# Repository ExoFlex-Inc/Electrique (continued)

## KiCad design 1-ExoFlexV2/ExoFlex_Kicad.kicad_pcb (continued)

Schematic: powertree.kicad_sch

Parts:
C3, C5, C12: 100uF 20% 35V; CAP_K1V101P_PAN; PART NUMBER EEE-FK1V101P
C4: 33uF 50V X7R; CAPC6153X500N; PART NUMBER KCM55WR71H336MH01L
C6: 2,2uF 35V X5R; C_0603_1608Metric; PART NUMBER GRM188R6YA225KA12D
C7, C8: 4,7uF 35V X7R; C_0805_2012Metric; PART NUMBER GRM21BZ7YA475KE15K
C9: 0,47uF 6,3V X5R; C_01005_0402Metric; PART NUMBER GRM022R60J474ME15L
C10: 47nF 6,3V X5R; C_01005_0402Metric; PART NUMBER GRM022R60J473ME15L
C11, C213, C214: 1uF 10% 20V; CAPMP3216X180N; PART NUMBER T491A105K020AT
C13, C14: 47uF 10V X5R; C_0805_2012Metric; PART NUMBER GRM21BR61A476ME15L
C15, C16: 330uF 10% 10V; CAPMP7.6X4.3_3.1N_KEM; PART NUMBER T495D337K010ATE150
D6, D9: TVS; DPY2_TEX; PART NUMBER TPD1E05U06DPYR
D116, D117, D118: LED; WL-SMCW_0603; PART NUMBER 150060RS75000
J5, J6: Jumper; PinHeader_1x03_P2.54mm_Vertical; PART NUMBER 61300311121
J7, J71: Jumper 5,2A; PinHeader_1x03_P2.54mm_Vertical; PART NUMBER MTLW-103-07-G-S-230
J8: USB-C; MOLEX_1054500101; PARTREV A7
J81: 14 AWG; PHOENIX_1755736; PART NUMBER 1755736
L1, L2: 1uH 20% 2,3A; L_1210_3225Metric; PART NUMBER BWQC003225161R0MH1
L3: 10uH 10% 150mA; INDC2012X145N; PART NUMBER LBR2012T100K
R5: 5.9k 1% 1/20W; R_0201_0603Metric; PART NUMBER ERJ-1GNF5901C
R6: 100 1% 1/10W; R_0603_1608Metric; PART NUMBER ERJ-3EKF1000V
R7: 8.45k 1% 1/20W; R_0201_0603Metric; PART NUMBER ERJ-1GNF8451C
R46, R47, R185: 270 1% 1/4W; R_0805_2012Metric; PART NUMBER ERJ-PB6B2700V
R55: 530 1% 0,1W; R_0603_1608Metric; PART NUMBER RN73H1JTTD5300F25
R57: 270 1% 1/10W; R_0603_1608Metric; PART NUMBER ERJ-3EKF2700V
R58: 820 1% 1/10W; R_0603_1608Metric; PART NUMBER ERJ-3EKF8200V
R73: 240 1% 1/10W; R_0603_1608Metric; PART NUMBER ERJ-3EKF2400V
R74: 720 1% 1/10W; R_0603_1608Metric; PART NUMBER CRCW0603720RFKTA
R76, R112: 5.1K 1% 1/10W; R_0603_1608Metric; PART NUMBER ERJ-3EKF5101V
TP6, TP7, TP8, TP9, TP10: TestPoint; KEYSTONE_5005; PART NUMBER 5005
U5: DCDC24V/8V; PTN78060WAD; PART NUMBER PTN78060WAD
U6: DCDC24V/5V NUM; NDY0011A_L; PART NUMBER LMZ23610TZ/NOPB
U7: DCDC 24V/-7,8V ANA; PTN78000; PART NUMBER PTN78000AAH
U14: TVS 24V; SOT-23-3_DBZ_TEX; PART NUMBER TSM36ADBZR
U123: LDO -5VA; TO92260P482H934-3N; PART NUMBER LM337LZ/LFT3
U124: LDO 5VA; T03B_TEX; PART NUMBER LM338T/NOPB

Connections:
+5V: J7.1, J8.A4 (VBUS_A4), J8.A9 (VBUS_A9), J8.B4 (VBUS_B4), J8.B9 (VBUS_B9), J71.1, J81.1; also elsewhere on the board
+5VA: J5.1; also elsewhere on the board
+24V: L1.1, L2.1, L3.1; also elsewhere on the board
-5VA: J6.1; also elsewhere on the board
GND: C3.2, C4.2, C5.2, C6.2, C7.2, C8.2, C9.2, C10.2, C11.2, C12.1, C13.2, C14.2, C15.2, C16.2, C213.2, C214.2, D6.2 (A), D9.2 (A), D116.1 (K), D117.1 (K), D118.2 (A), J8.A1 (GND_A1), J8.A12 (GND_A12), J8.B1 (GND_B1), J8.B12 (GND_B12), J8.SH1 (SHIELD3), J8.SH2 (SHIELD4), J8.SH3 (SHIELD1), J8.SH4 (SHIELD2), J81.2, R5.1, R6.1, R58.1, R74.1, R76.1, R112.2, U5.1 (GND), U5.7 (GND), U6.3 (SYNC), U6.5 (AGND), U6.6 (AGND), U6.12 (EP), U7.P5 (GND), U14.1 (GND), U14.2 (GND); also elsewhere on the board
unnamed: C4.1, L1.2, U6.1 (VIN), U6.2 (VIN)
unnamed: C5.1, C7.1, C8.1, L3.2, U7.P2 (VIN)
unnamed: C6.1, L2.2, U5.2 (VI)
unnamed: C9.1, U6.8 (SS)
unnamed: C10.1, C13.1, C14.1, C15.1, C16.1, J7.2, J71.2, R55.2, R185.2, TP9.TP, U6.10 (VOUT), U6.11 (VOUT), U14.3 (IO)
unnamed: C11.1, C12.2, R7.1, TP6.TP, U7.P1 (VOUT), U123.3 (IN)
unnamed: C3.1, C213.1, TP10.TP, U5.5 (SENSE), U5.6 (VO), U124.3 (IN)
unnamed: C214.1, D9.1 (K), J6.2, R47.2, R73.2, TP8.TP, U123.2 (OUT)
unnamed: D6.1 (K), J5.2, R46.2, R57.2, TP7.TP, U124.2 (OUT)
unnamed: D116.2 (A), R185.1
unnamed: D117.2 (A), R46.1
unnamed: D118.1 (K), R47.1
unnamed: J7.3, J71.3
unnamed: J8.A5 (CC1), R76.2
unnamed: J8.B5 (CC2), R112.1
unnamed: R5.2, U5.4 (VOADJUST)
unnamed: R7.2, U7.P4 (SET)
unnamed: R6.2, R55.1, U6.7 (FB)
unnamed: R57.1, R58.2, U124.1 (ADJ)
unnamed: R73.1, R74.2, U123.1 (ADJ)

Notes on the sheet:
REV 1
__HS HERE__
15/07/2024 - Louis-Daniel Gaulin
Vers PI5 5V
Régulateur 5VNUM: 24V @ 1,45A Régulateur 5VA : 24 @ 110mA Régulateur -5VA : 24 @ 25mA Contacteur : 24V @ 110mA Total Current : 24V @ 1,695A

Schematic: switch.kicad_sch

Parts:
D39, D40, D41, D42, D47, D48, D49, D50, D55, D56: TVS; DPY2_TEX; PART NUMBER TPD1E05U06DPYR
J25, J26, J27, J28, J29, J30, J31, J32, J33, J34: 2POS; CON_39281023; PART NUMBER 0039281023
R11, R12, R13, R14, R15, R16, R17, R18, R19, R20: 1K 1% 1/10W; R_0603_1608Metric; PART NUMBER ERJ-3EKF1001V

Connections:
+5V: R11.2, R12.2, R13.2, R14.2, R15.2, R16.2, R17.2, R18.2, R19.2, R20.2; also elsewhere on the board
GND: D39.2 (A), D40.2 (A), D41.2 (A), D42.2 (A), D47.2 (A), D48.2 (A), D49.2 (A), D50.2 (A), D55.2 (A), D56.2 (A); also elsewhere on the board
MAX_SW_1: D39.1 (K), J25.2; also elsewhere on the board
MAX_SW_2: D41.1 (K), J27.2; also elsewhere on the board
MAX_SW_3: D47.1 (K), J29.2; also elsewhere on the board
MAX_SW_4: D49.1 (K), J31.2; also elsewhere on the board
MAX_SW_5: D50.1 (K), J32.2; also elsewhere on the board
MIN_SW_1: D40.1 (K), J26.2; also elsewhere on the board
MIN_SW_2: D42.1 (K), J28.2; also elsewhere on the board
MIN_SW_3: D48.1 (K), J30.2; also elsewhere on the board
unnamed: J25.1, R14.1
unnamed: J26.1, R11.1
unnamed: J27.1, R12.1
unnamed: J28.1, R13.1
unnamed: J29.1, R15.1
unnamed: J30.1, R16.1
unnamed: J31.1, R17.1
unnamed: J32.1, R18.1
unnamed: J33.1, R19.1
unnamed: J34.1, R20.1
RESET: D56.1 (K), J34.2; also elsewhere on the board
URG_USER: D55.1 (K), J33.2; also elsewhere on the board

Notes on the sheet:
RESET
SWMIN2
URG1
SWMAX3
SWMIN1
SWMAX1
SWMIN3
10xRes1k : 5V @ 50mA Total current : 5V @ 52,5mA
SWMAX5
SWMAX4
SWMAX2

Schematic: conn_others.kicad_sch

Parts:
D100, D101, D102, D103, D104, D106, D108: TVS; DPY2_TEX; PART NUMBER TPD1E05U06DPYR
J52: 2POS; CON_39281023; PART NUMBER 0039281023
J53, J54: 3POS; CON_39301039; PARTREV 03.03.2021
J57: 6POS; PinSocket_1x06_P2.54mm_Vertical; PART NUMBER SMC-1-06-1-GT

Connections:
+5V: D104.1 (K), J57.1; also elsewhere on the board
+5VA: J53.3, J54.3; also elsewhere on the board
/CONNECTOR (OTHERS)/CANH: D101.1 (K), J52.1, J57.5
/CONNECTOR (OTHERS)/CANL: D103.1 (K), J52.2, J57.6
CAN_RD: D100.1 (K), J57.4; also elsewhere on the board
CAN_TD: D102.1 (K), J57.3; also elsewhere on the board
GND: D100.2 (A), D101.2 (A), D102.2 (A), D103.2 (A), D104.2 (A), D106.2 (A), D108.2 (A), J53.1, J54.1, J57.2; also elsewhere on the board
TEMP_OUT_1: D106.1 (K), J53.2; also elsewhere on the board
TEMP_OUT_2: D108.1 (K), J54.2; also elsewhere on the board

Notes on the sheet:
Notes :
Bus Adapter : 5V @ 75mA 2xTempSensor : N/A (uA) Total current : 5V @ 78,75mA
Temp 2
CAN Bus
Temp 1

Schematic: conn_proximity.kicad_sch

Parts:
D59, D60, D61, D62, D67, D68, D69, D70, D71, D72, D73, D74: TVS; DPY2_TEX; PART NUMBER TPD1E05U06DPYR
J35, J36, J37, J38: 2POS; CON_39281023; PART NUMBER 0039281023
J39, J40, J41, J42: 4POS; CON_39301049; PARTREV 03.03.2021
R21, R22, R23, R24: 1K 1% 1/10W; R_0603_1608Metric; PART NUMBER ERJ-3EKF1001V
R25, R26, R27, R28: 100K 1% 1/10W; R_0603_1608Metric; PART NUMBER ERJ-3EKF1003V
R114, R120: 165 1% 1/20W; R_0201_0603Metric; PART NUMBER ERJ-1GNF1650C
R119, R168: 464 1% 1/20W; R_0201_0603Metric; PART NUMBER ERJ-1GNF4640C

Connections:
+5V: R21.2, R22.2, R23.2, R24.2, R25.1, R26.1, R27.1, R28.1, R114.1, R119.1, R120.1, R168.1; also elsewhere on the board
BUT_PROX_LEFT1: D59.1 (K), J35.2; also elsewhere on the board
BUT_PROX_LEFT2: D60.1 (K), J36.2; also elsewhere on the board
BUT_PROX_RIGHT1: D61.1 (K), J37.2; also elsewhere on the board
BUT_PROX_RIGHT2: D62.1 (K), J38.2; also elsewhere on the board
EMI_PROX1: D71.1 (K), J39.2
EMI_PROX1_INT: D67.1 (K), J39.4, R25.2; also elsewhere on the board
EMI_PROX2: D73.1 (K), J41.2
EMI_PROX2_INT: D69.1 (K), J41.4, R27.2; also elsewhere on the board
GND: D59.2 (A), D60.2 (A), D61.2 (A), D62.2 (A), D67.2 (A), D68.2 (A), D69.2 (A), D70.2 (A), D71.2 (A), D72.2 (A), D73.2 (A), D74.2 (A), J39.1, J40.1, J41.1, J42.1; also elsewhere on the board
unnamed: J35.1, R21.1
unnamed: J36.1, R22.1
unnamed: J37.1, R23.1
unnamed: J38.1, R24.1
unnamed: J39.3, R114.2
unnamed: J40.3, R119.2
unnamed: J41.3, R120.2
unnamed: J42.3, R168.2
REC_PROX1: D72.1 (K), J40.2; also elsewhere on the board
REC_PROX1_INT: D68.1 (K), J40.4, R26.2; also elsewhere on the board
REC_PROX2: D74.1 (K), J42.2; also elsewhere on the board
REC_PROX2_INT: D70.1 (K), J42.4, R28.2; also elsewhere on the board

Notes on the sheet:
Emi Prox 2
But Prox L2
Rec Prox 1
Emi Prox 1
But Prox R1
Rec Prox 2
But Prox R2
But Prox L1
4xRes1k : 5V @ 20mA 4xRes100k : 5V @ 0,2mA 2x165 : 5V @ 30mA 2x464 : 5V @ 10,7mA Total current : 5V @ 64mA

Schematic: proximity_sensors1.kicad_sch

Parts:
C38, C39, C40, C41: 10uF 10V X7R; C_0805_2012Metric; PART NUMBER GRM21BR71A106KA73L
C42, C43: 10nF 50V; C_0805_2012Metric; PART NUMBER GRM2195C1H103JA01D
J95, J96, J97, J98, J99, J100: Jumper; PinHeader_1x03_P2.54mm_Vertical; PART NUMBER 61300311121
R121, R122, R123, R124: 10K 1% 1/10W; R_0603_1608Metric; PART NUMBER ERJ-3EKF1002V
R125, R126, R127, R128: 5.1K 1% 1/10W; R_0603_1608Metric; PART NUMBER ERJ-3EKF5101V
R129, R130: 0Ω; R_0805_2012Metric; PART NUMBER ERJ-6GEY0R00V
R131, R132, R133, R134, R135, R136: 100K 1% 1/10W; R_0603_1608Metric; PART NUMBER ERJ-3EKF1003V
TP92, TP93: TestPoint; KEYSTONE_5005; PART NUMBER 5005
U45, U46, U47: Inverter; SN74LVC3G14DCUT; PART NUMBER SN74LVC3G14DCUT
U62, U63, U64, U65: AND Gate; SOT95P270X145-5N; PART NUMBER SN74LVC1G08DBVR

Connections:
+5V: R131.2, R132.2, R133.2, R134.2, R135.2, R136.2, U45.8 (VCC), U46.8 (VCC), U47.8 (VCC), U62.5 (VCC), U63.5 (VCC), U64.5 (VCC), U65.5 (VCC); also elsewhere on the board
BUT_PROX_LEFT1: R121.1, R125.1; also elsewhere on the board
BUT_PROX_LEFT2: R122.1, R126.1; also elsewhere on the board
BUT_PROX_RIGHT1: R123.1, R127.1; also elsewhere on the board
BUT_PROX_RIGHT2: R124.1, R128.1; also elsewhere on the board
GND: C38.2, C39.2, C40.2, C41.2, C42.2, C43.2, R121.2, R122.2, R123.2, R124.2, U45.4 (GND), U46.4 (GND), U46.5 (2Y), U46.6 (3A), U47.3 (2A), U47.4 (GND), U47.6 (3A), U62.3 (GND), U63.3 (GND), U64.3 (GND), U65.3 (GND); also elsewhere on the board
M_BUT_PROX_L1: J98.2, U64.1 (A); also elsewhere on the board
M_BUT_PROX_L2: J97.2, U64.2 (B); also elsewhere on the board
M_BUT_PROX_R1: J95.2, U62.1 (A); also elsewhere on the board
M_BUT_PROX_R2: J99.2, U62.2 (B); also elsewhere on the board
M_REC_PROX1: J100.2, U63.1 (A); also elsewhere on the board
M_REC_PROX2: J96.2, U63.2 (B); also elsewhere on the board
unnamed: C38.1, R125.2, U45.1 (1A)
unnamed: C39.1, R126.2, U45.3 (2A)
unnamed: C40.1, R127.2, U45.6 (3A)
unnamed: C41.1, R128.2, U46.1 (1A)
unnamed: C42.1, J100.1, R129.2
unnamed: C43.1, J96.1, R130.2
unnamed: J95.1, U45.2 (3Y)
unnamed: J95.3, R131.1
unnamed: J96.3, R132.1
unnamed: J97.1, U45.5 (2Y)
unnamed: J97.3, R133.1
unnamed: J98.1, U45.7 (1Y)
unnamed: J98.3, R134.1
unnamed: J99.1, U46.7 (1Y)
unnamed: J99.3, R135.1
unnamed: J100.3, R136.1
unnamed: U47.1 (1A), U65.4 (Y)
unnamed: U62.4 (Y), U65.2 (B)
unnamed: U64.4 (Y), U65.1 (A)
PROX_BUT_SEC: TP92.TP, U47.7 (1Y); also elsewhere on the board
PROX_OPTO_SEC: TP93.TP, U63.4 (Y); also elsewhere on the board
REC_PROX1: R129.1; also elsewhere on the board
REC_PROX2: R130.1; also elsewhere on the board

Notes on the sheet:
Do not populate
4xANDGate : 5V @ 4mA 5xNOTGate : 5V @ 5mA Total current : 5V @ 9,55mA
Debouncing

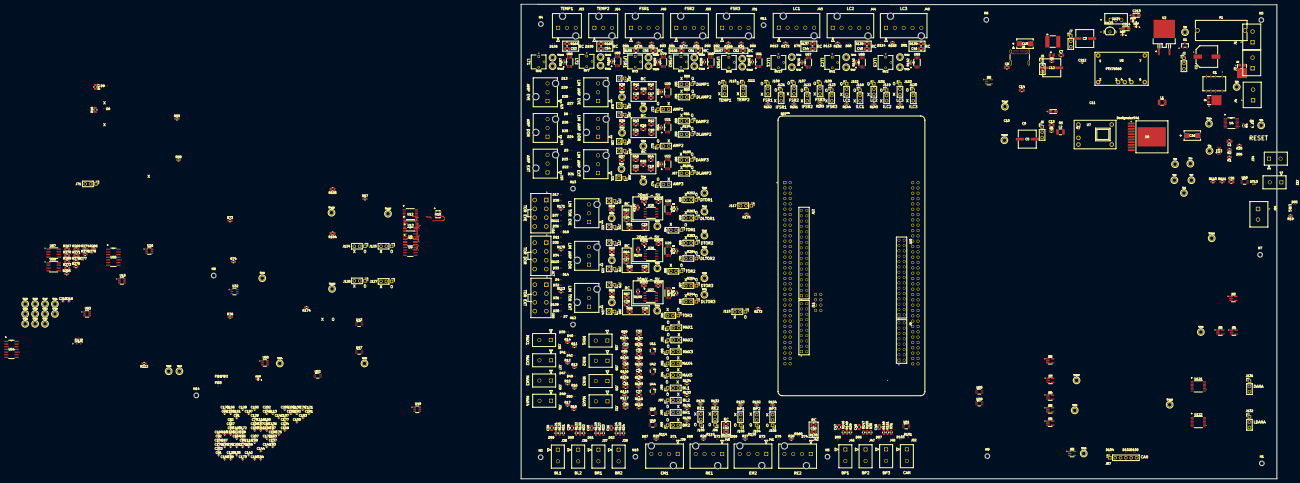
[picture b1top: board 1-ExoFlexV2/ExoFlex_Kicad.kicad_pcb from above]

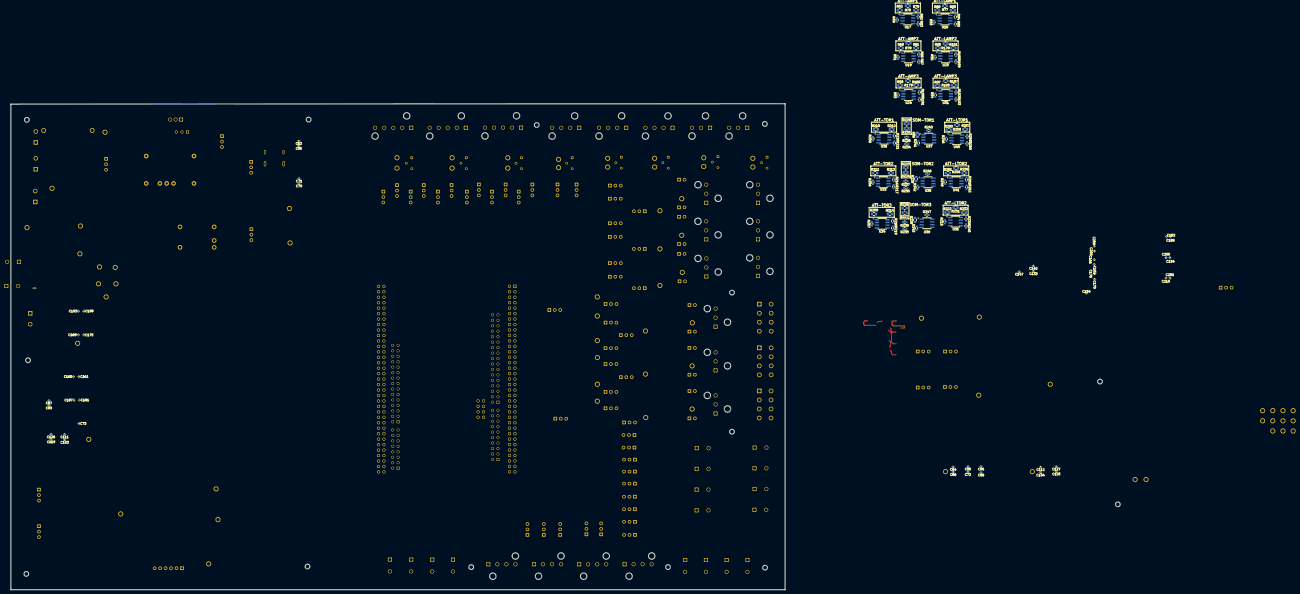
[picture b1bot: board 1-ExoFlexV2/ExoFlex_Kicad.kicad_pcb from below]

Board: 4 copper layers, 360.3 x 226.2 mm, 849 parts (150 on the bottom side), 438 nets.

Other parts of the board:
J55, J56, J58, J59, J66, J67: Jumper; PinHeader_1x03_P2.54mm_Vertical
R49, R50, R51, R82, R83, R84, R85, R86, R87, R92, R93, R94, R188, R189, R190, R191, R192, R193: 10K 1% 1/10W; R_0603_1608Metric
R52, R68, R69, R70, R77, R78, R95, R96, R97, R178, R179, R180: 3.3k 1% 1/8W; R_0805_2012Metric
R79, R80, R81, R181, R186, R187: 0Ω; R_0805_2012Metric
R88, R90, R91, R194, R195, R196: 100k 1% 1/20W; R_0201_0603Metric
U17, U18, U19, U23, U24, U31: OP_AMP2; SOIC127P599X175-8N

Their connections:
+5VA: U17.8 (VCC+), U18.8 (VCC+), U19.8 (VCC+), U23.8 (VCC+), U24.8 (VCC+), U31.8 (VCC+); also elsewhere on the board
-5VA: U17.4 (VCC-), U18.4 (VCC-), U19.4 (VCC-), U23.4 (VCC-), U24.4 (VCC-), U31.4 (VCC-); also elsewhere on the board
DOR_AMP_DATA: J58.2; also elsewhere on the board
DOR_AMP_DATA1: R51.1; also elsewhere on the board
DOR_AMP_LIM_DATA: J59.2; also elsewhere on the board
DOR_AMP_LIM_DATA1: R92.1; also elsewhere on the board
EVE_AMP_DATA: J55.2; also elsewhere on the board
EVE_AMP_DATA1: R49.1; also elsewhere on the board
EVE_AMP_LIM_DATA: J56.2; also elsewhere on the board
EVE_AMP_LIM_DATA1: R50.1; also elsewhere on the board
EXT_AMP_DATA: J66.2; also elsewhere on the board
EXT_AMP_DATA1: R93.1; also elsewhere on the board
EXT_AMP_LIM_DATA: J67.2; also elsewhere on the board
EXT_AMP_LIM_DATA1: R94.1; also elsewhere on the board
GND: R88.2, R90.2, R91.2, R194.2, R195.2, R196.2, U17.3 (1IN+), U17.5 (2IN+), U18.3 (1IN+), U18.5 (2IN+), U19.3 (1IN+), U19.5 (2IN+), U23.3 (1IN+), U23.5 (2IN+), U24.3 (1IN+), U24.5 (2IN+), U31.3 (1IN+), U31.5 (2IN+); also elsewhere on the board
unnamed: J55.1, R83.1, U17.7 (2OUT)
unnamed: J55.3, R88.1
unnamed: J56.1, R85.1, U18.7 (2OUT)
unnamed: J56.3, R90.1
unnamed: J58.1, R87.1, U19.7 (2OUT)
unnamed: J58.3, R91.1
unnamed: J59.1, R189.1, U23.7 (2OUT)
unnamed: J59.3, R194.1
unnamed: J66.1, R191.1, U24.7 (2OUT)
unnamed: J66.3, R195.1
unnamed: J67.1, R193.1, U31.7 (2OUT)
unnamed: J67.3, R196.1
unnamed: R49.2, R52.1, U17.2 (1IN-)
unnamed: R50.2, R68.1, U18.2 (1IN-)
unnamed: R51.2, R69.1, U19.2 (1IN-)
unnamed: R52.2, R70.1
unnamed: R68.2, R77.1
unnamed: R69.2, R78.1
unnamed: R70.2, R79.1
unnamed: R77.2, R80.1
unnamed: R78.2, R81.1
unnamed: R79.2, R82.2, U17.1 (1OUT)
unnamed: R80.2, R84.2, U18.1 (1OUT)
unnamed: R81.2, R86.2, U19.1 (1OUT)
unnamed: R82.1, R83.2, U17.6 (2IN-)
unnamed: R84.1, R85.2, U18.6 (2IN-)
unnamed: R86.1, R87.2, U19.6 (2IN-)
unnamed: R92.2, R95.1, U23.2 (1IN-)
unnamed: R93.2, R96.1, U24.2 (1IN-)
unnamed: R94.2, R97.1, U31.2 (1IN-)
unnamed: R95.2, R178.1
unnamed: R178.2, R181.1
unnamed: R96.2, R179.1
unnamed: R179.2, R186.1
unnamed: R97.2, R180.1
unnamed: R180.2, R187.1
unnamed: R181.2, R188.2, U23.1 (1OUT)
unnamed: R186.2, R190.2, U24.1 (1OUT)
unnamed: R187.2, R192.2, U31.1 (1OUT)
unnamed: R188.1, R189.2, U23.6 (2IN-)
unnamed: R190.1, R191.2, U24.6 (2IN-)
unnamed: R192.1, R193.2, U31.6 (2IN-)

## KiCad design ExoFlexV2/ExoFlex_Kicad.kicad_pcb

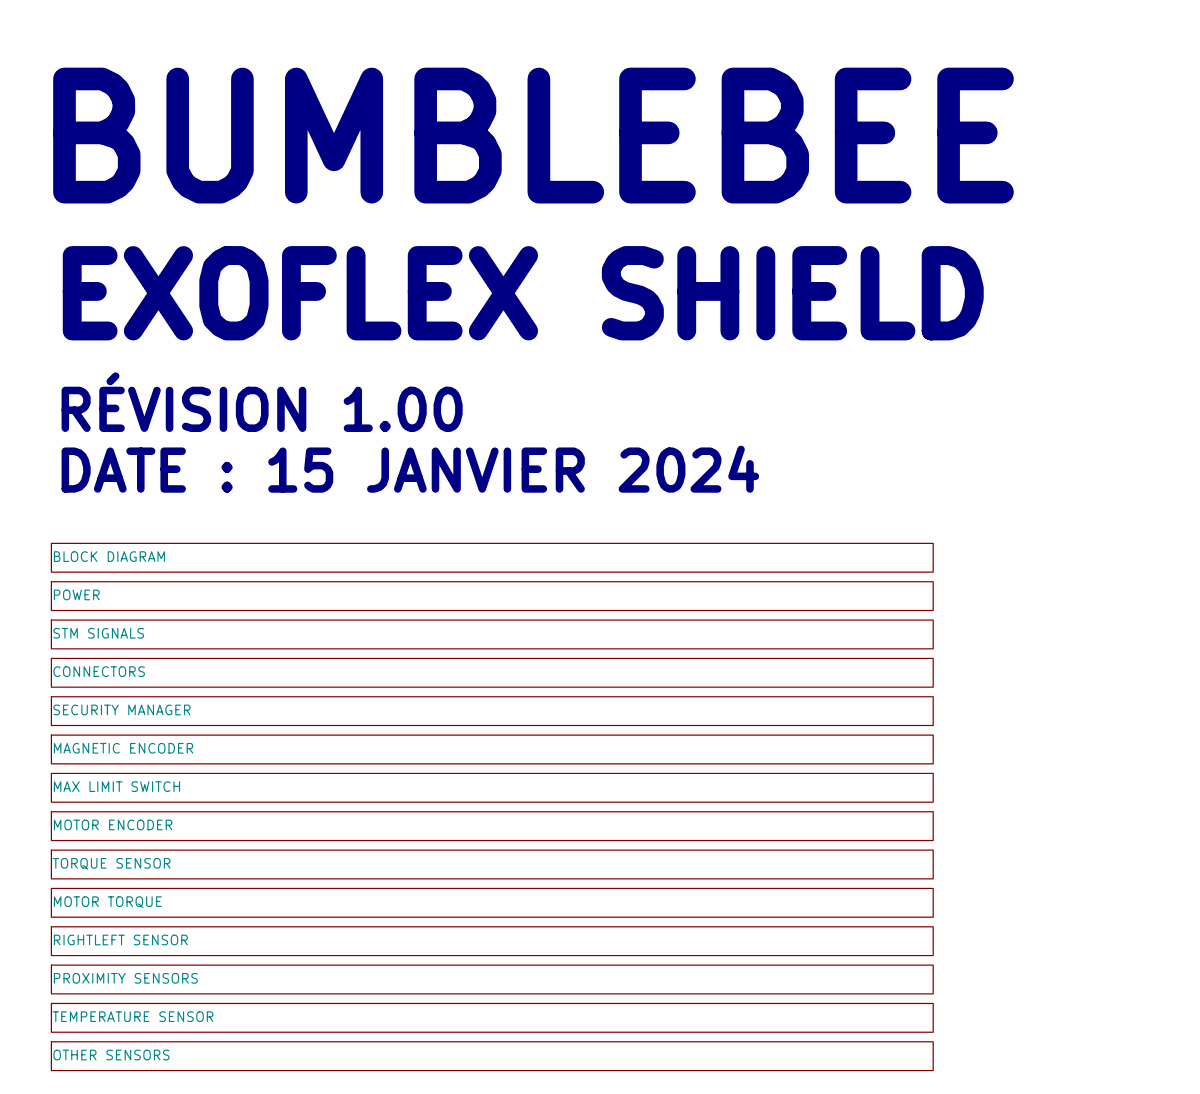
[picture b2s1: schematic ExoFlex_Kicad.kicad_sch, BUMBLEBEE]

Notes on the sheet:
BUMBLEBEE
EXOFLEX SHIELD
RÉVISION 1.00 DATE : 15 JANVIER 2024

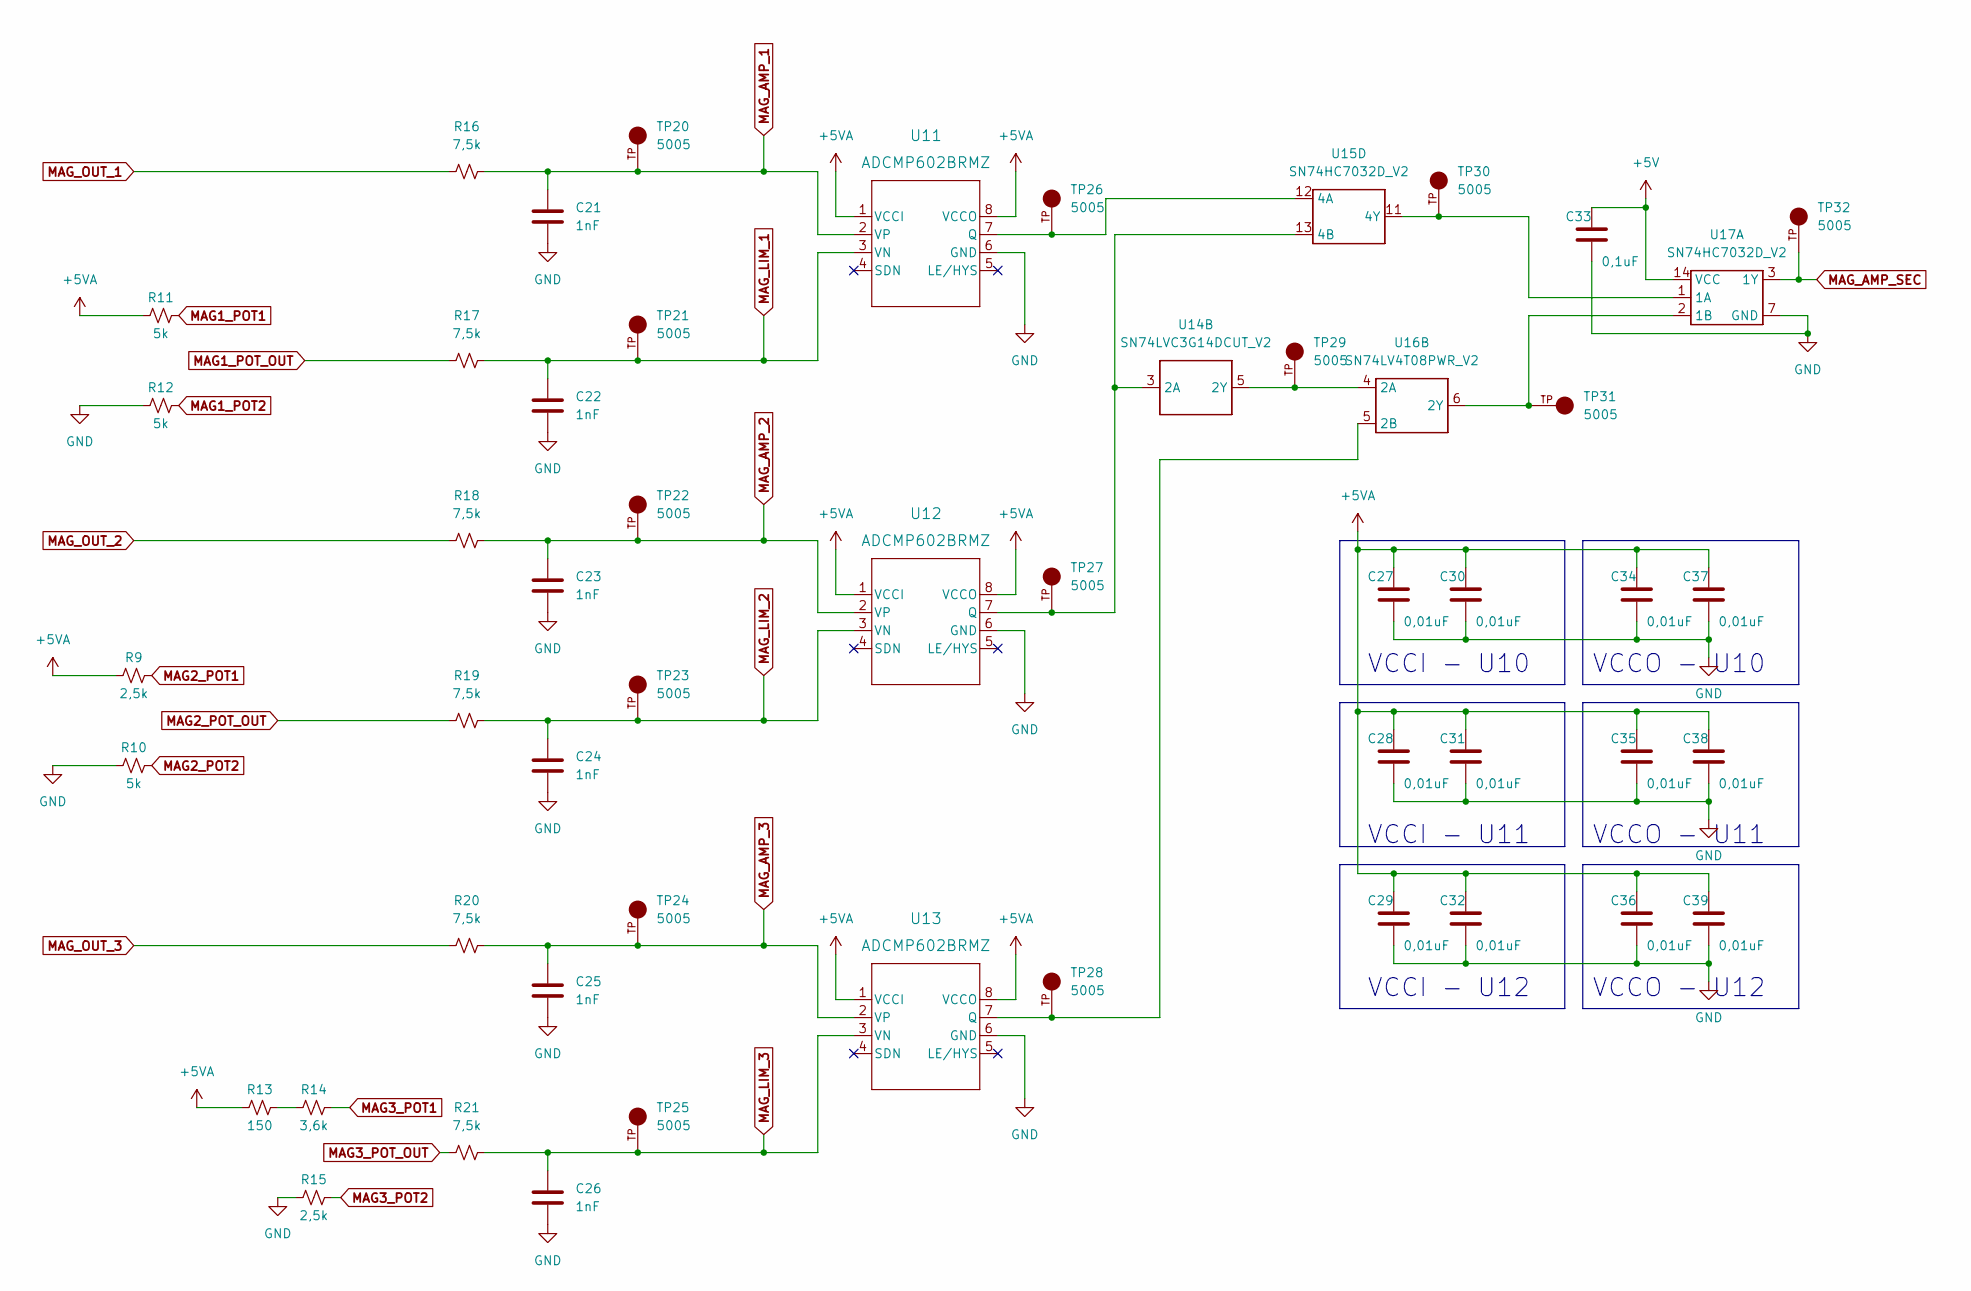
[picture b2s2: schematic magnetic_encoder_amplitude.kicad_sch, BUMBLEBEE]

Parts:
C21, C22, C23, C24, C25, C26: 1nF; C_0603_1608Metric
C27, C28, C29, C30, C31, C32, C34, C35, C36, C37, C38, C39: 0,01uF; C_0603_1608Metric
C33: 0,1uF; C_0603_1608Metric
R9, R15: 2,5k; R_0603_1608Metric
R10, R11, R12: 5k; R_0603_1608Metric
R13: 150; R_0603_1608Metric
R14: 3,6k; R_0603_1608Metric
R16, R17, R18, R19, R20, R21: 7,5k; R_0603_1608Metric
TP20, TP21, TP22, TP23, TP24, TP25, TP26, TP27, TP28, TP29, TP30, TP31, TP32: 5005; KEYSTONE_5005
U11, U12, U13: ADCMP602BRMZ
U14: SN74LVC3G14DCUT_V2; SN74LVC3G14DCUT
U15, U17: SN74HC7032D_V2; SN74HC7032D
U16: SN74LV4T08PWR_V2; SN74LV4T08PWR

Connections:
+5VA: C27.1, C28.1, C29.1, C30.1, C31.1, C32.1, C34.1, C35.1, C36.1, C37.1, C38.1, C39.1, R9.1, R11.1, R13.1, U11.1 (VCCI), U11.8 (VCCO), U12.1 (VCCI), U12.8 (VCCO), U13.1 (VCCI), U13.8 (VCCO); also elsewhere on the board
MAG1_POT1: R11.2; also elsewhere on the board
MAG1_POT2: R12.2; also elsewhere on the board
MAG1_POT_OUT: R17.1; also elsewhere on the board
MAG2_POT1: R9.2; also elsewhere on the board
MAG2_POT2: R10.2; also elsewhere on the board
MAG2_POT_OUT: R19.1; also elsewhere on the board
MAG3_POT1: R14.2; also elsewhere on the board
MAG3_POT2: R15.2; also elsewhere on the board
MAG3_POT_OUT: R21.1; also elsewhere on the board
MAG_AMP_1: C21.1, R16.2, TP20.TP, U11.2 (VP); also elsewhere on the board
MAG_AMP_2: C23.1, R18.2, TP22.TP, U12.2 (VP); also elsewhere on the board
MAG_AMP_3: C25.1, R20.2, TP24.TP, U13.2 (VP); also elsewhere on the board
MAG_AMP_SEC: TP32.TP, U17.3 (1Y); also elsewhere on the board
MAG_LIM_1: C22.1, R17.2, TP21.TP, U11.3 (VN); also elsewhere on the board
MAG_LIM_2: C24.1, R19.2, TP23.TP, U12.3 (VN); also elsewhere on the board
MAG_LIM_3: C26.1, R21.2, TP25.TP, U13.3 (VN); also elsewhere on the board
MAG_OUT_1: R16.1; also elsewhere on the board
MAG_OUT_2: R18.1; also elsewhere on the board
MAG_OUT_3: R20.1; also elsewhere on the board
unnamed: R13.2, R14.1
unnamed: TP26.TP, U11.7 (Q), U15.12 (4A)
unnamed: TP27.TP, U12.7 (Q), U14.3 (2A), U15.13 (4B)
unnamed: TP28.TP, U13.7 (Q), U16.5 (2B)
unnamed: TP29.TP, U14.5 (2Y), U16.4 (2A)
unnamed: TP30.TP, U15.11 (4Y), U17.1 (1A)
unnamed: TP31.TP, U16.6 (2Y), U17.2 (1B)

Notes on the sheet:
VCCO - U11
VCCO - U10
VCCI - U10
VCCO - U12
VCCI - U11
VCCI - U12

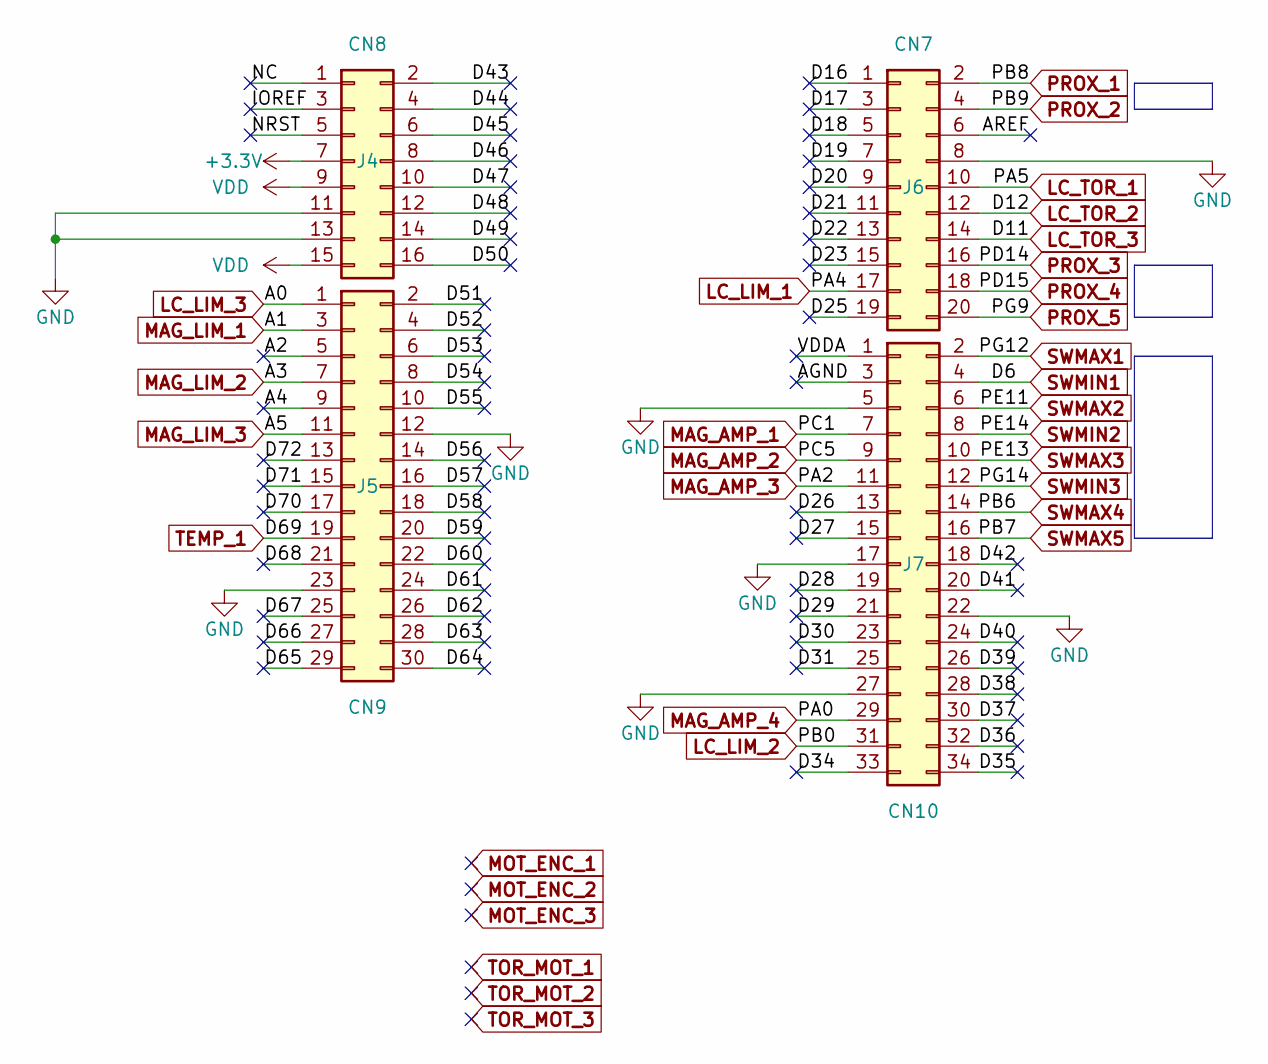
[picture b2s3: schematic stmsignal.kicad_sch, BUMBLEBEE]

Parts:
J4: CN8; PinSocket_2x08_P2.54mm_Vertical
J5: CN9; PinSocket_2x15_P2.54mm_Vertical
J6: CN7; PinSocket_2x10_P2.54mm_Vertical
J7: CN10; PinSocket_2x17_P2.54mm_Vertical

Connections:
+3V3: J4.7
/STM SIGNALS/A2: J5.5
/STM SIGNALS/A4: J5.9
/STM SIGNALS/AGND: J7.3
/STM SIGNALS/AREF: J6.6
/STM SIGNALS/D16: J6.1
/STM SIGNALS/D17: J6.3
/STM SIGNALS/D18: J6.5
/STM SIGNALS/D19: J6.7
/STM SIGNALS/D20: J6.9
/STM SIGNALS/D21: J6.11
/STM SIGNALS/D22: J6.13
/STM SIGNALS/D23: J6.15
/STM SIGNALS/D25: J6.19
/STM SIGNALS/D26: J7.13
/STM SIGNALS/D27: J7.15
/STM SIGNALS/D28: J7.19
/STM SIGNALS/D29: J7.21
/STM SIGNALS/D30: J7.23
/STM SIGNALS/D31: J7.25
/STM SIGNALS/D34: J7.33
/STM SIGNALS/D35: J7.34
/STM SIGNALS/D36: J7.32
/STM SIGNALS/D37: J7.30
/STM SIGNALS/D38: J7.28
/STM SIGNALS/D39: J7.26
/STM SIGNALS/D40: J7.24
/STM SIGNALS/D41: J7.20
/STM SIGNALS/D42: J7.18
/STM SIGNALS/D43: J4.2
/STM SIGNALS/D44: J4.4
/STM SIGNALS/D45: J4.6
/STM SIGNALS/D46: J4.8
/STM SIGNALS/D47: J4.10
/STM SIGNALS/D48: J4.12
/STM SIGNALS/D49: J4.14
/STM SIGNALS/D50: J4.16
/STM SIGNALS/D51: J5.2
/STM SIGNALS/D52: J5.4
/STM SIGNALS/D53: J5.6
/STM SIGNALS/D54: J5.8
/STM SIGNALS/D55: J5.10
/STM SIGNALS/D56: J5.14
/STM SIGNALS/D57: J5.16
/STM SIGNALS/D58: J5.18
/STM SIGNALS/D59: J5.20
/STM SIGNALS/D60: J5.22
/STM SIGNALS/D61: J5.24
/STM SIGNALS/D62: J5.26
/STM SIGNALS/D63: J5.28
/STM SIGNALS/D64: J5.30
/STM SIGNALS/D65: J5.29
/STM SIGNALS/D66: J5.27
/STM SIGNALS/D67: J5.25
/STM SIGNALS/D68: J5.21
/STM SIGNALS/D70: J5.17
/STM SIGNALS/D71: J5.15
/STM SIGNALS/D72: J5.13
/STM SIGNALS/IOREF: J4.3
/STM SIGNALS/NC: J4.1
/STM SIGNALS/NRST: J4.5
/STM SIGNALS/VDDA: J7.1
LC_LIM_1: J6.17; also elsewhere on the board
LC_LIM_2: J7.31; also elsewhere on the board
LC_LIM_3: J5.1; also elsewhere on the board
LC_TOR_1: J6.10; also elsewhere on the board
LC_TOR_2: J6.12; also elsewhere on the board
LC_TOR_3: J6.14; also elsewhere on the board
MAG_AMP_1: J7.7; also elsewhere on the board
MAG_AMP_2: J7.9; also elsewhere on the board
MAG_AMP_3: J7.11; also elsewhere on the board
MAG_AMP_4: J7.29; also elsewhere on the board
MAG_LIM_1: J5.3; also elsewhere on the board
MAG_LIM_2: J5.7; also elsewhere on the board
MAG_LIM_3: J5.11; also elsewhere on the board
PROX_1: J6.2; also elsewhere on the board
PROX_2: J6.4; also elsewhere on the board
PROX_3: J6.16; also elsewhere on the board
PROX_4: J6.18; also elsewhere on the board
PROX_5: J6.20; also elsewhere on the board
SWMAX1: J7.2; also elsewhere on the board
SWMAX2: J7.6; also elsewhere on the board
SWMAX3: J7.10; also elsewhere on the board
SWMAX4: J7.14; also elsewhere on the board
SWMAX5: J7.16; also elsewhere on the board
SWMIN1: J7.4; also elsewhere on the board
SWMIN2: J7.8; also elsewhere on the board
SWMIN3: J7.12; also elsewhere on the board
TEMP_1: J5.19; also elsewhere on the board
VDD: J4.9, J4.15

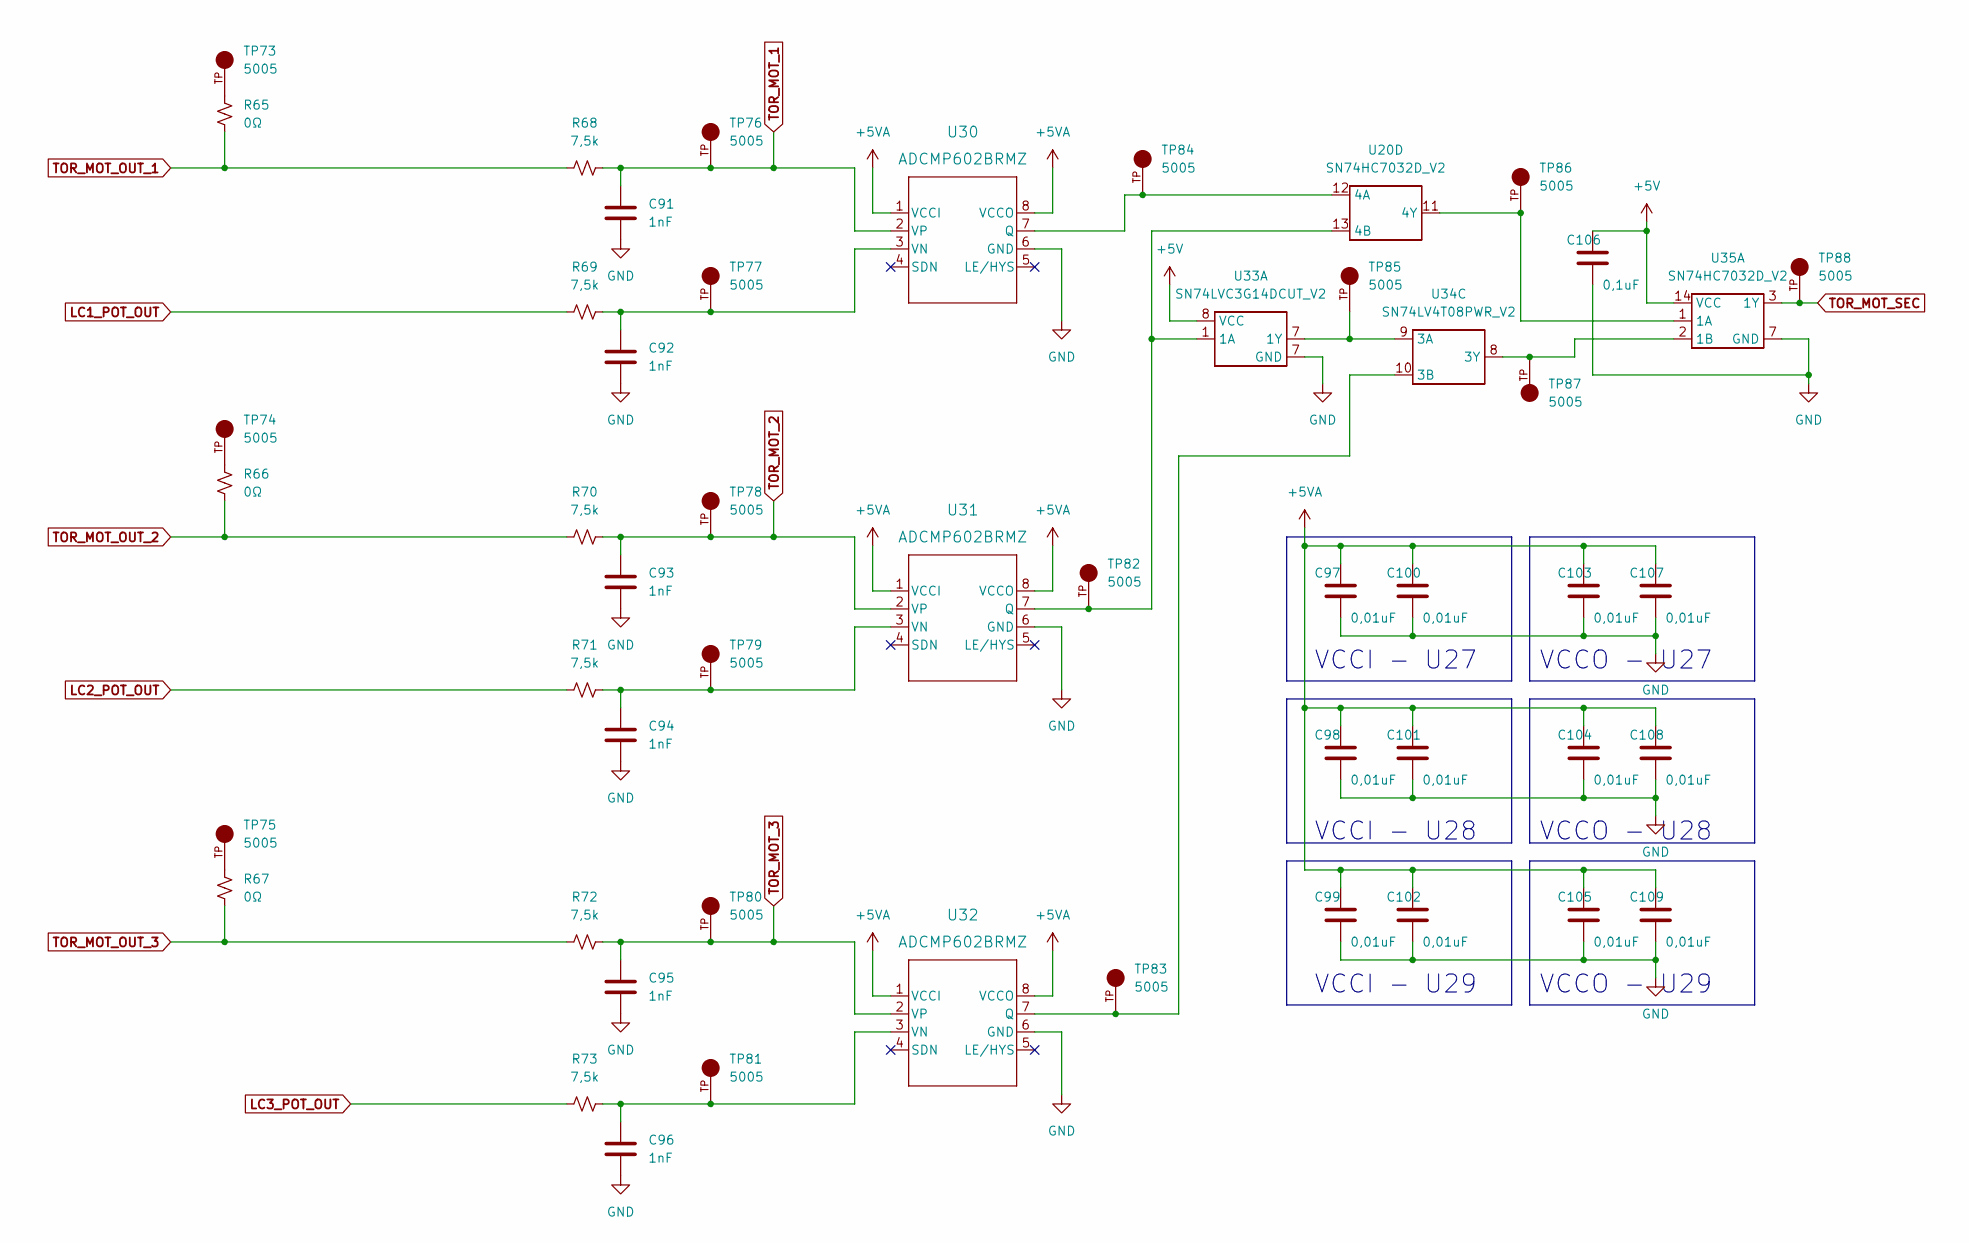
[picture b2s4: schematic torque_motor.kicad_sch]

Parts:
C91, C92, C93, C94, C95, C96: 1nF; C_0603_1608Metric
C97, C98, C99, C100, C101, C102, C103, C104, C105, C107, C108, C109: 0,01uF; C_0603_1608Metric
C106: 0,1uF; C_0603_1608Metric
R65, R66, R67: 0Ω; R_0603_1608Metric
R68, R69, R70, R71, R72, R73: 7,5k; R_0603_1608Metric
TP73, TP74, TP75, TP76, TP77, TP78, TP79, TP80, TP81, TP82, TP83, TP84, TP85, TP86, TP87, TP88: 5005; KEYSTONE_5005
U20, U35: SN74HC7032D_V2; SN74HC7032D
U30, U31, U32: ADCMP602BRMZ
U33: SN74LVC3G14DCUT_V2; SN74LVC3G14DCUT
U34: SN74LV4T08PWR_V2; SN74LV4T08PWR

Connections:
+5VA: C97.1, C98.1, C99.1, C100.1, C101.1, C102.1, C103.1, C104.1, C105.1, C107.1, C108.1, C109.1, U30.1 (VCCI), U30.8 (VCCO), U31.1 (VCCI), U31.8 (VCCO), U32.1 (VCCI), U32.8 (VCCO); also elsewhere on the board
LC1_POT_OUT: R69.1; also elsewhere on the board
LC2_POT_OUT: R71.1; also elsewhere on the board
LC3_POT_OUT: R73.1; also elsewhere on the board
unnamed: C92.1, R69.2, TP77.TP, U30.3 (VN)
unnamed: C94.1, R71.2, TP79.TP, U31.3 (VN)
unnamed: C96.1, R73.2, TP81.TP, U32.3 (VN)
unnamed: R65.1, TP73.TP
unnamed: R66.1, TP74.TP
unnamed: R67.1, TP75.TP
unnamed: TP82.TP, U20.13 (4B), U31.7 (Q), U33.1 (1A)
unnamed: TP83.TP, U32.7 (Q), U34.10 (3B)
unnamed: TP84.TP, U20.12 (4A), U30.7 (Q)
unnamed: TP86.TP, U20.11 (4Y), U35.1 (1A)
unnamed: TP87.TP, U34.8 (3Y), U35.2 (1B)
TOR_MOT_1: C91.1, R68.2, TP76.TP, U30.2 (VP)
TOR_MOT_2: C93.1, R70.2, TP78.TP, U31.2 (VP)
TOR_MOT_3: C95.1, R72.2, TP80.TP, U32.2 (VP)
TOR_MOT_OUT_1: R65.2, R68.1; also elsewhere on the board
TOR_MOT_OUT_2: R66.2, R70.1; also elsewhere on the board
TOR_MOT_OUT_3: R67.2, R72.1; also elsewhere on the board
TOR_MOT_SEC: TP88.TP, U35.3 (1Y); also elsewhere on the board

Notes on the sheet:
VCCI - U27
VCCO - U28
VCCI - U29
VCCO - U27
VCCI - U28
VCCO - U29
